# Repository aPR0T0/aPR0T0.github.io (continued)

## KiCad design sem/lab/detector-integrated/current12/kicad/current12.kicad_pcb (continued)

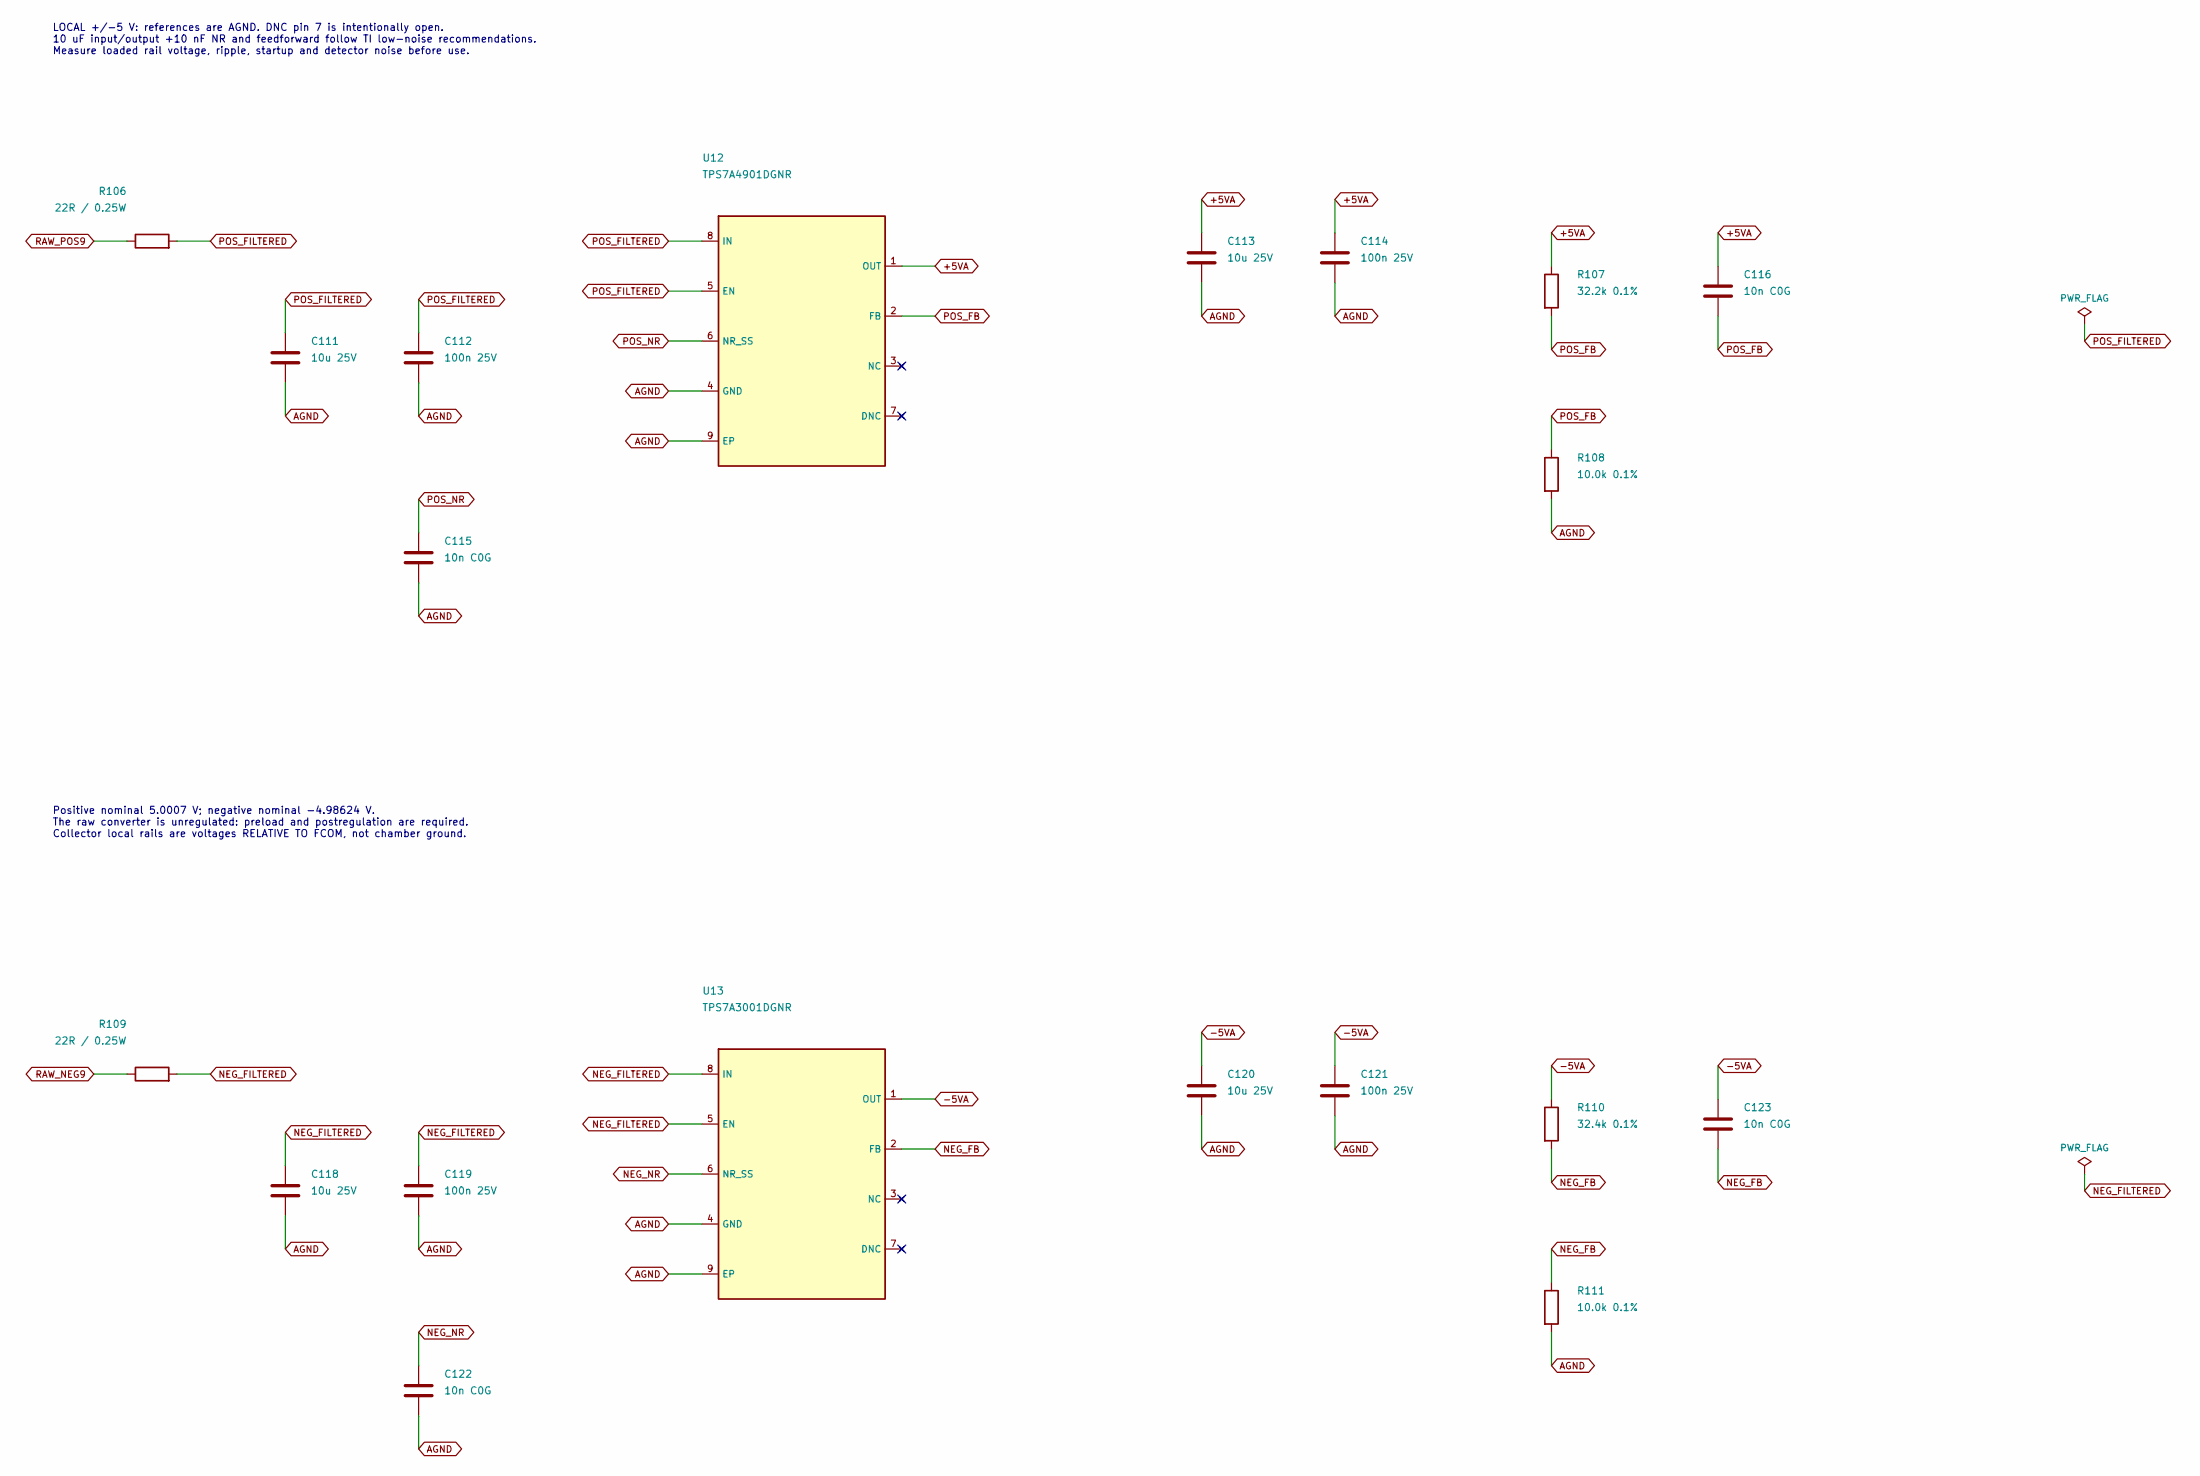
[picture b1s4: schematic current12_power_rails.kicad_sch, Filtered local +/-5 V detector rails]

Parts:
C111, C113, C118, C120: 10u 25V; C_1210_3225Metric
C112, C114, C119, C121: 100n 25V; C_0805_2012Metric
C115, C116, C122, C123: 10n C0G; C_0805_2012Metric
R106, R109: 22R / 0.25W; R_1206_3216Metric
R107: 32.2k 0.1%; R_0805_2012Metric
R108, R111: 10.0k 0.1%; R_0805_2012Metric
R110: 32.4k 0.1%; R_0805_2012Metric
U12: TPS7A4901DGNR; TPS7A_DGN8_TI; MPN TPS7A4901DGNR
U13: TPS7A3001DGNR; TPS7A_DGN8_TI; MPN TPS7A3001DGNR

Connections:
+5VA: C113.1, C114.1, C116.1, R107.1, U12.1 (OUT); also elsewhere on the board
-5VA: C120.1, C121.1, C123.1, R110.1, U13.1 (OUT); also elsewhere on the board
AGND: C111.2, C112.2, C113.2, C114.2, C115.2, C118.2, C119.2, C120.2, C121.2, C122.2, R108.2, R111.2, U12.4 (GND), U12.9 (EP), U13.4 (GND), U13.9 (EP); also elsewhere on the board
NEG_FB: C123.2, R110.2, R111.1, U13.2 (FB)
NEG_FILTERED: C118.1, C119.1, R109.2, U13.5 (EN), U13.8 (IN)
NEG_NR: C122.1, U13.6 (NR_SS)
POS_FB: C116.2, R107.2, R108.1, U12.2 (FB)
POS_FILTERED: C111.1, C112.1, R106.2, U12.5 (EN), U12.8 (IN)
POS_NR: C115.1, U12.6 (NR_SS)
RAW_NEG9: R109.1; also elsewhere on the board
RAW_POS9: R106.1; also elsewhere on the board

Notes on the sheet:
LOCAL +/-5 V: references are AGND. DNC pin 7 is intentionally open. 10 uF input/output +10 nF NR and feedforward follow TI low-noise recommendations. Measure loaded rail voltage, ripple, startup and detector noise before use.
Positive nominal 5.0007 V; negative nominal -4.98624 V. The raw converter is unregulated: preload and postregulation are required. Collector local rails are voltages RELATIVE TO FCOM, not chamber ground.

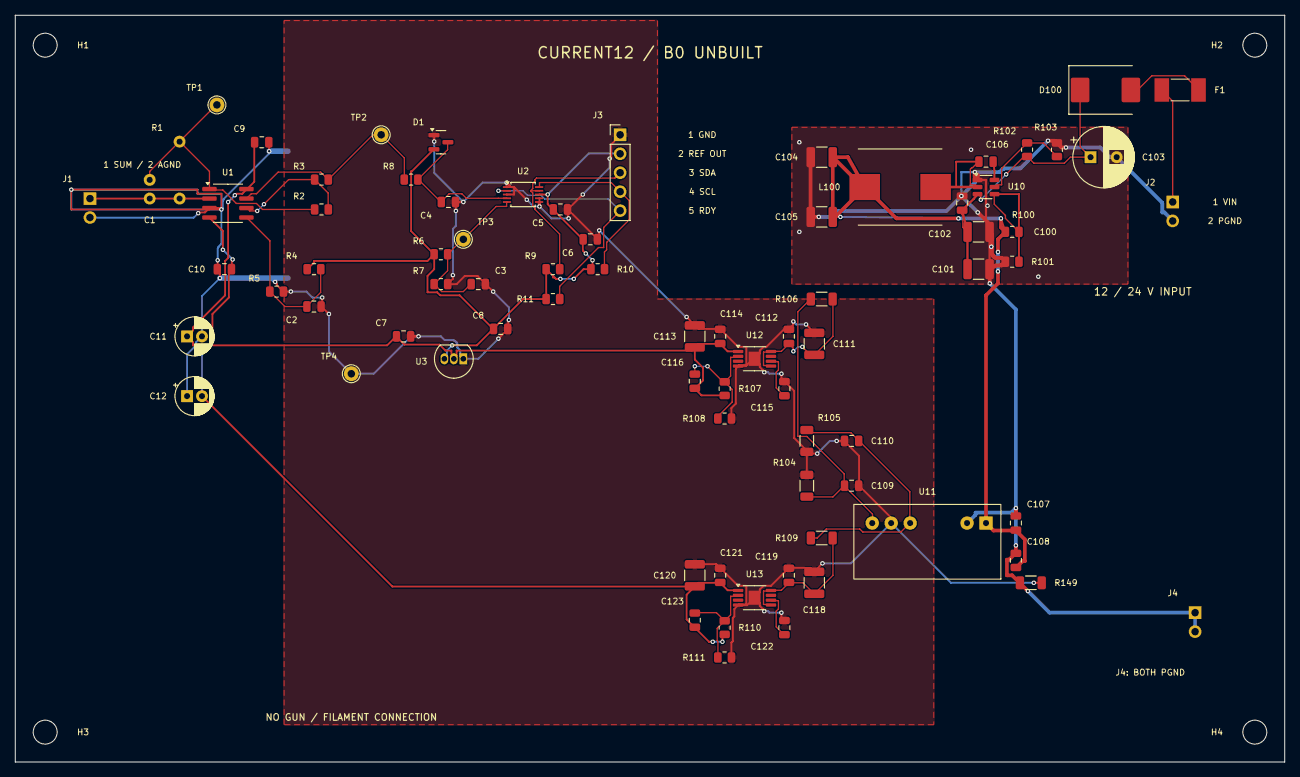
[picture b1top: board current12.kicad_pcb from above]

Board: 2 copper layers, 170.0 x 100.0 mm, 82 parts (0 on the bottom side), 31 nets.

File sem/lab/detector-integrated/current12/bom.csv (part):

Reference,Value,Quantity,MPN_or_procurement_spec,Footprint,Function,Datasheet
U1,LMC662AIM,1,LMC662AIMX/NOPB,Package_SO:SOIC-8_3.9x4.9mm_P1.27mm,"Dual CMOS TIA / attenuator; solder directly, no socket",https://www.ti.com/lit/ds/symlink/lmc662.pdf
R1,100M 1%,1,HVA05FA100M,Resistor_THT:R_Axial_DIN0207_L6.3mm_D2.5mm_P7.62mm_Horizontal,100M axial 6x2.5mm body; tolerance calibrates,
C1,10p C0G,1,10p C0G,Capacitor_THT:C_Disc_D3.0mm_W1.6mm_P2.50mm,"TIA stability, tau=1ms nominal; real input capacitance must be tested",
J1,SPECIMEN / SHIELD,1,SPECIMEN / SHIELD,Connector_PinHeader_2.54mm:PinHeader_1x02_P2.54mm_Vertical,"Direct solder PTFE coax preferred; 1 specimen, 2 shield/chamber",
R2,40.2k 0.1%,1,40.2k 0.1%,Resistor_SMD:R_0805_2012Metric,Attenuator input,
R3,10.0k 0.1%,1,10.0k 0.1%,Resistor_SMD:R_0805_2012Metric,Attenuator feedback,
R4,15.0k 0.1%,1,15.0k 0.1%,Resistor_SMD:R_0805_2012Metric,VBIAS upper divider,
R5,10.0k 0.1%,1,10.0k 0.1%,Resistor_SMD:R_0805_2012Metric,VBIAS lower divider,
C2,1u 10V X7R,1,1u 10V X7R,Capacitor_SMD:C_0805_2012Metric,Quiet 1.32V filter,
R6,1.00k 0.1%,1,1.00k 0.1%,Resistor_SMD:R_0805_2012Metric,ADC midpoint divider upper / rail bleeder,
R7,1.00k 0.1%,1,1.00k 0.1%,Resistor_SMD:R_0805_2012Metric,ADC midpoint divider lower,
C3,10u 10V X7R,1,10u 10V X7R,Capacitor_SMD:C_0805_2012Metric,1.65V reference filter,
R8,820R,1,820R,Resistor_SMD:R_0805_2012Metric,ADC overload current limit; downstream of sensitive node,
C4,100n,1,100n,Capacitor_SMD:C_0805_2012Metric,ADC local RC filter,
D1,BAT54S,1,BAT54S,Package_TO_SOT_SMD:SOT-23,ADC-only Schottky clamp; never on SUM,https://assets.nexperia.com/documents/data-sheet/BAT54S.pdf
U2,ADS1115IDGS,1,ADS1115IDGSR,Package_SO:TSSOP-10_3x3mm_P0.5mm,Differential AIN0-AIN1; I2C0x48; PGA +/-256mV 128SPS defaults,https://www.ti.com/lit/ds/symlink/ads1115.pdf
R9,4.7k,1,4.7k,Resistor_SMD:R_0805_2012Metric,I2C pull-up,
R10,4.7k,1,4.7k,Resistor_SMD:R_0805_2012Metric,I2C pull-up,
R11,10k,1,10k,Resistor_SMD:R_0805_2012Metric,Optional ready open-drain pull-up,
C5,100n,1,100n,Capacitor_SMD:C_0805_2012Metric,ADC local bypass,
C6,1u 10V,1,1u 10V,Capacitor_SMD:C_0805_2012Metric,ADC local bulk bypass,
J3,ESP32 I2C / REF,1,ESP32 I2C / REF,Connector_PinHeader_2.54mm:PinHeader_1x05_P2.54mm_Vertical,1GND 2REF3V3OUT 3GPIO21 4GPIO22 5RDY optional (NC default); ESP powered separately,
U3,MCP1700-3302E/TO,1,MCP1700-3302E/TO,Package_TO_SOT_THT:TO-92_Inline,3.3V ADC supply derived from +5V; max input6V,https://www.microchip.com/content/dam/mchp/documents/APID/Pr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
C7,1u 10V,1,1u 10V,Capacitor_SMD:C_0805_2012Metric,LDO input bypass,
C8,1u 10V,1,1u 10V,Capacitor_SMD:C_0805_2012Metric,LDO required output capacitor,
C9,100n,1,100n,Capacitor_SMD:C_0805_2012Metric,LMC positive rail local bypass,
C10,100n,1,100n,Capacitor_SMD:C_0805_2012Metric,LMC negative rail local bypass,
C11,10u 16V,1,10u 16V,Capacitor_THT:CP_Radial_D5.0mm_P2.00mm,Positive rail bulk; positive lead to+5V,
C12,10u 16V,1,10u 16V,Capacitor_THT:CP_Radial_D5.0mm_P2.00mm,Negative rail bulk; positive lead toAGND,
TP1,TIA,1,TIA,TestPoint:TestPoint_THTPad_D2.0mm_Drill1.0mm,Low impedance measurement only,
TP2,ADC_DRIVE,1,ADC_DRIVE,TestPoint:TestPoint_THTPad_D2.0mm_Drill1.0mm,Low impedance measurement only,
TP3,VMID,1,VMID,TestPoint:TestPoint_THTPad_D2.0mm_Drill1.0mm,Low impedance measurement only,
TP4,AGND,1,AGND,TestPoint:TestPoint_THTPad_D2.0mm_Drill1.0mm,Low impedance measurement only,
H1,M3,1,M3,MountingHole:MountingHole_3.2mm_M3,Unplated mounting hole; insulating standoff,
H2,M3,1,M3,MountingHole:MountingHole_3.2mm_M3,Unplated mounting hole; insulating standoff,
H3,M3,1,M3,MountingHole:MountingHole_3.2mm_M3,Unplated mounting hole; insulating standoff,
H4,M3,1,M3,MountingHole:MountingHole_3.2mm_M3,Unplated mounting hole; insulating standoff,
J4,CHAMBER / OUTER SHIELD,1,CHAMBER / OUTER SHIELD,Connector_PinHeader_2.54mm:PinHeader_1x02_P2.54mm_Vertical,"Chamber, enclosure, outer shield; never FCOM",
J2,12/24V DC INPUT,1,12/24V DC INPUT,Connector_PinHeader_2.54mm:PinHeader_1x02_P2.54mm_Vertical,1: positive regulated 9-30 V DC; 2: return. Current-limited source; no mains input.,
F1,1A FAST / 125V,1,0451001.MRL,Fuse:Fuse_Littelfuse-NANO2-451_453,Input wiring/fault fuse; verify converter and input-capacitor inrush against time-current and I-squared-t limits.,https://www.littelfuse.com/products/fuses-overcurrent-protec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
D100,SS36 / 60V,1,SS36-E3/57T,Diode_SMD:D_SMC,"Series reverse-input protection. Pin 1 cathode to protected input; pin 2 anode to fuse. This exact Vishay part is SMC, not SMA.",https://www.vishay.com/docs/88751/ss32.pdf
C100,4.7u 50V,1,4.7u 50V,Capacitor_SMD:C_1210_3225Metric,First buck input capacitor: direct short loop to U10 VIN/GND.,
C101,4.7u 50V,1,4.7u 50V,Capacitor_SMD:C_1210_3225Metric,Second buck input capacitor; total nominal input 9.4 uF.,
C102,100n 50V,1,100n 50V,Capacitor_SMD:C_0805_2012Metric,HF input bypass; shortest possible VIN-to-GND loop.,
C103,22u 50V,1,22u 50V,Capacitor_THT:CP_Radial_D8.0mm_P3.50mm,"22 uF 50 V aluminum, body <=8 mm, leads formed to 3.5 mm pitch; connector-side input bulk. Positive at protected input.",
U10,LMR51420XF,1,LMR51420XFDDCR,Package_TO_SOT_SMD:SOT-23-6,"500 kHz forced-PWM synchronous buck, 4.5-36 V operating. 9-30 V regulated input is the board limit; no automotive surge qualification.",https://www.ti.com/lit/ds/symlink/lmr51420.pdf
L100,10uH / 12A Isat,1,SRP1038A-100M,Integrated:Bourns_SRP1038A,"10 uH, 7.5 A RMS, 12 A Isat, 30 mOhm max. Isat exceeds 5.1 A maximum buck current-limit threshold. Nonpolar.",https://www.bourns.com/docs/product-datasheets/srp1038a.pdf
C104,22u 25V,1,22u 25V,Capacitor_SMD:C_1210_3225Metric,X7R; verify effective capacitance at operating voltage,
C105,22u 25V,1,22u 25V,Capacitor_SMD:C_1210_3225Metric,X7R; verify effective capacitance at operating voltage,
C106,100n 25V,1,100n 25V,Capacitor_SMD:C_0805_2012Metric,Bootstrap capacitor directly between U10 pin 6 CB and pin 2 SW.,
R100,101k 0.1%,1,101k 0.1%,Resistor_SMD:R_0805_2012Metric,Buck feedback top: 0.6*(1+101/13.5) = 5.08889 V nominal. Both divider resistors must be 0.1% to preserve the reviewed module/supervisor voltage margin.,
R101,13.5k 0.1%,1,13.5k 0.1%,Resistor_SMD:R_0805_2012Metric,Buck feedback bottom; Kelvin reference to PGND at input-capacitor return.,
R102,1.00M 1%,1,1.00M 1%,Resistor_SMD:R_0805_2012Metric,"EN divider top: nominal 7.38 V rising UVLO, below accepted 9 V input after series diode.",
R103,200k 1%,1,200k 1%,Resistor_SMD:R_0805_2012Metric,EN divider bottom; about 6.6 V falling UVLO. EN cannot float.,
U11,R05P09D/P,1,R05P09D/P,Integrated:R05P09D_SIP7,"5 V to unregulated +/-9 V, 55 mA each; 1 W. Basic 250 VAC rms working isolation, 4-10 pF; 6.4 kV DC is a 1-second test only. /P gives continuous short protection.",https://www.recom-power.com/pdf/Econoline/RxxPxx.pdf
C107,1u 25V,1,1u 25V,Capacitor_SMD:C_0805_2012Metric,Local primary bypass at the isolation module input pins.,
C108,100n 25V,1,100n 25V,Capacitor_SMD:C_0805_2012Metric,HF primary bypass; does not cross the isolation barrier.,
C109,1u 25V,1,1u 25V,Capacitor_SMD:C_0805_2012Metric,X7R; verify effective capacitance at operating voltage,
C110,1u 25V,1,1u 25V,Capacitor_SMD:C_0805_2012Metric,X7R; verify effective capacitance at operating voltage,
R104,1.30k / 0.25W,1,1.30k / 0.25W,Resistor_SMD:R_1206_3216Metric,Raw positive preload >=6.23 mA at 8.1 V (>10% of 55 mA rail rating).,
R105,1.30k / 0.25W,1,1.30k / 0.25W,Resistor_SMD:R_1206_3216Metric,Raw negative preload. Validate cross-regulation with actual asymmetric load.,
R149,0R STAR BOND,1,0R STAR BOND,Resistor_SMD:R_1206_3216Metric,Intentional single-point ground bond for near-ground specimen detector. Fitted 0 ohm; omitted entirely on collector variant.,
R106,22R / 0.25W,1,22R / 0.25W,Resistor_SMD:R_1206_3216Metric,Series differential ripple filter; 22 ohm with 10 uF gives a 723 Hz nominal pole. Raw preload is before this resistor.,
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
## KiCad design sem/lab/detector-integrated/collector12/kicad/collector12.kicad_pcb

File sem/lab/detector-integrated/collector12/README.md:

# Biased-collector board · collector12

Collector12 · B0 · unbuilt. A separate metal collector measures net arriving electron current. The bias converter raises FCOM, which is the common for the amplifier, ADC and local MCU. Two onboard optocouplers connect that floating section to the grounded scan ESP32.

Input: 12 / 24 V · regulated 9–30 V. Local rails: ±5 V around FCOM · local 3.3 V.

## Exact external connections

Connector pin numbers, not screen orientation, define the wiring. Pin 1 uses the marked / square pad in the native footprint. Match this revision before assembly.

| Pin | Net | External connection | Detail |
|---|---|---|---|
| J2.1 | VIN | DC source +12 V or +24 V | Use regulated 9–30 V; this powers detector electronics and bias only. |
| J2.2 | PGND | DC source negative | Ground-side return. |
| J1.1 | SUM | Separate metal collector | Insulated feedthrough centre. Never connect the bias output directly to this pin. |
| J1.2 | FCOM | Inaccessible inner guard | Floats near +200 V. Keep the outer cable shield and enclosure separately grounded. |
| J3.1 | PGND | ESP32 GND | All J3 pins are on the grounded side. |
| J3.2 | HOST_VIO | ESP32 3.3 V rail | Required interface supply INPUT, ≤19 mA planning allowance. Using the host’s rail removes the board-powered LED/pull-up injection path; leakage and hot-plug behavior remain unverified. |
| J3.3 | HOST_TX | ESP32 GPIO17 · UART TX | Host → optocoupler → floating MCU RX. |
| J3.4 | HOST_RX | ESP32 GPIO16 · UART RX | Floating MCU TX → optocoupler → host. |
| J3.5 | HV_ENABLE | ESP32 GPIO32 | LOW by default. HIGH enables the current-limited bias supply; actual rail qualification still holds the command clamp. |
| J3.6 | PGM_RELEASE | ESP32 GPIO33 | LOW clamps programming to zero. HIGH only after startup; hardware also requires the actual module rail to pass its delayed check. |
| J3.7 | HV_FAULT_N | ESP32 GPIO34 · input | Active-LOW current-limiter fault; board pulls up to HOST_VIO. A fault blanks acquisition and disables bias. |
| J3.8 | PGND | ESP32 GND / optional duplicate return | Same ground-side net as J3.1. |
| J4.1 | PGND | Chamber / enclosure ground star | Ground the specimen in this collector-only arrangement. Accessible metal also needs its own secure earth bond. |
| J4.2 | PGND | Same ground star / shield return | Duplicate PGND terminal; keep this separate from the floating inner guard. |
| J5.1 | MISO | AVR programmer MISO · only with bias discharged | Standard 2×3 ICSP; remove every programmer lead before bias operation. |
| J5.2 | +3V3D | Programmer target-voltage sense | 3.3 V logic only; do not back-power the island. |
| J5.3 | SCK | AVR programmer SCK | Configure an external 8 MHz crystal and suitable ICSP clock. |
| J5.4 | MOSI | AVR programmer MOSI | Commission with HV disabled and verified discharged. |
| J5.5 | RESET | AVR programmer RESET | Not a ground-side control signal. |
| J5.6 | FCOM | AVR programmer ground · commissioning only | Disconnect programmer entirely before collector bias is enabled. |

## Design files

- Open `kicad/collector12.kicad_pro` with KiCad 10. The complete design ZIP includes all hierarchical sheets and local libraries.
- `exports/schematic.pdf` contains every schematic sheet.
- `exports/assembly.svg` identifies the component positions.
- `bom.csv` contains the selected parts; prices are not quoted.
- `verification/check-summary.json` records native checks and checked-file hashes.
- `fabrication.zip` contains prototype manufacturing outputs. Inspection and bench commissioning remain required.

Collector firmware and setup notes are in the firmware folder of the complete package. J3.2 is a HOST_VIO **input** from the ESP32’s own 3.3 V rail. The two UART paths use onboard optocouplers.

---

## Shared architecture and commissioning

Two unbuilt PCB prototypes extend the original LMC662 / ADS1115 detector. Use the [interactive board and pin guide](https://apr0t0.github.io/sem/lab/power.html) to select specimen current or the positive collector. Both accept a regulated 9–30 V input, including nominal 12 V and 24 V. This supply powers detector electronics and collector bias; the electron gun, scan drivers and grounded ESP32 have separate supplies.

## What is onboard

Input fuse and reverse-polarity diode → LMR51420 500 kHz buck → approximately 5.09 V → RECOM R05P09D/P isolated raw ±9 V → RC filtering → TPS7A49 / TPS7A30 local ±5 V. The ADC runs from its own 3.3 V supply regulator. The collector also has a separate digital 3.3 V rail, an ATmega328P and two VO2611-X016 optocouplers.

The collector's XP Power CA02P-5 module is soldered onto the same board. It creates programmable 0–200 V from the onboard 5 V bus. Two 10 kΩ filter stages and 100 nF / 1 µF capacitors feed FCOM. Nominal FCOM at a raw 200 V is about 199.6 V because of bleeder loading. A TPS2553-1 latch-off switch limits the bias-module input: 88.7 kΩ / 1% programs a calculated 262–342 mA range, below the module’s 420 mA short-protection input limit. Its active-LOW fault goes through J3.7 to ESP32 GPIO34. Verify startup and current-limit behavior on the assembled board. Program linearity is specified from 15% of full scale, so treat low-bias settings as requiring calibration.

The isolated supply and HV converter are packaged modules; the buck is a discrete IC / inductor circuit. This is a self-contained onboard power design, not an entirely discrete magnetics design. Obtain current distributor quotes: the HV module may dominate cost.

Both layouts use local top/bottom PGND copper and six stitching vias around the buck's ground returns. The amplifier's C9/C10 bypass capacitors have direct 0.75 mm returns to the quiet AGND or FCOM plane. The guarded SUM trace and its no-plane region remain separate. These filled-copper connections were inspected in the native boards; their noise performance still requires measurement.

## Choose the current path

| Connection | Specimen-current board | Collector board |
|---|---|---|
| J1.1 SUM | Insulated conductive specimen holder | Separate insulated metal collector |
| J1.2 guard | AGND, near chamber ground | FCOM, near positive collector bias |
| Specimen | Only through SUM; insulated from stage | Grounded conductive contact |
| Local analog common | Deliberately bonded to PGND/chamber | Elevated FCOM |
| J3 data | Direct 3.3 V I²C to ESP32 | Ground-side UART through two optocouplers |
| Extra bias | None | Generated and filtered onboard |

The specimen-current board’s direct I²C is not isolated during power-off. Keep both host and detector powered while connected, using coordinated power; disconnect the interface before separately power-cycling either side. The collector uses host-powered VIO at J3.2 for its ground-side UART interface.

SUM is the amplifier input. The positive bias connects to FCOM, never directly to SUM; a direct bias wire would bypass the measurement. At steady state, unsaturated feedback holds SUM close to the amplifier's local common. The collector reading is net collected electron current, potentially a mixture of SE, BSE and background. There is no charge multiplication on a plain metal collector. An insulating specimen still needs a charging solution.

## Collector boundary

The complete analog circuit, ADS1115 and ATmega328P operate relative to FCOM. The primary side, CA converter case/return, outer enclosure, accessible cable shield, grounded specimen and scan ESP32 operate relative to chamber ground. Only the rated isolated converter, two optocouplers and deliberate filtered bias network bridge these references. No grounded USB, programming or oscilloscope cable belongs on FCOM while biased.

Mount the collector PCB on nylon / PEEK standoffs with insulating fasteners. Four 3.2 mm holes reserve a maximum 6.4 mm diameter insulating washer envelope. A grounded screw head is not an electrically neutral hole: maintain separation from grounded metal above and below the floating copper.

The PCB design enforces a 5 mm copper separation between primary and FCOM regions and a separate 2 mm rule between grounded-side HV and low-voltage conductors. These are layout rules, not certification. RECOM's 250 VAC rms basic working insulation is the relevant published working specification; 6.4 kV is a brief test rating. Converter and optocoupler capacitance still carries displacement current. Rail filters cannot remove every path for common-mode pickup.

## Collector startup and shutdown

1. Verify component orientations, cleanliness, connector numbering and the exact BOM. Assemble and inspect the input power stages before fitting the high-impedance parts where practical.
2. With the electron beam blanked and the HV module disabled, power from a current-limited regulated source. Verify 5 V bus, ±9 V raw rails, ±5 V local rails and both 3.3 V domains using their correct reference. Repeat at 12 V and 24 V and across expected loads.
3. Program the ATmega328P for an external 8 MHz crystal and 3.3 V operation with bias disabled and verified discharged. Remove all ICSP connections. Connect the grounded ESP32 via the specified UART, two control pins and active-LOW fault input. Feed collector J3.2 HOST_VIO from the ESP32’s 3.3 V rail (allow 19 mA); this removes the board-powered LED/pull-up injection path into host GPIO. Leakage and hot-plug behavior remain unverified. On the specimen-current board, J3.2 is instead a reference output and is left open.
4. Begin with the bias pot at minimum. The ESP32 first confirms the optical link. Its `b` command raises HV_ENABLE while holding PGM_RELEASE LOW for at least 100 ms, then releases the buffered RC ramp. Hardware also uses a TPS3808G50 to qualify the actual module 5 V rail, with a datasheet delay of 180–420 ms before allowing PGM_RELEASE to release the clamp. The buffer remains powered from the unswitched 5 V bus. A 10 kΩ / 47 µF command filter gives about 0.47–0.59 s nominal ramp time; effective capacitance and leakage must be checked. The sketch keeps the beam blanked for a 10 s initial settling policy and checks the optical link during that interval. That delay is a starting policy, not a guarantee of pA settling. Measure the actual bias rise, overshoot and settling before deciding the interval is adequate.
5. With bias steady and beam blanked, use `z` to measure a new zero. Only then use `s` for a scan. Repeat zero after any bias adjustment. The acquisition sequence requests fresh ADC conversions; CRC, request IDs, status and timeouts reject incomplete or stale replies.
6. `x` aborts, blanks the beam, clamps programming to zero and removes the CA module's 5 V input. Passive bleeders remain connected. Check voltage with a rated instrument before touching or attaching a programmer; a software OFF state is not proof of discharge.

The final 1 µF capacitor alone stores 20 mJ at 200 V. Its independent 9.98 MΩ bleeder has a 9.98 s time constant, but additional paths and unspecified module internal capacitance affect whole-assembly discharge. Measure the complete assembly, including cables and relevant faults. These software controls are not a certified beam interlock.

## Proving that readings are electrons

- Inject a known local current into SUM at zero bias and elevated bias. Establish gain, sign, offset, clipping and settling with the real cable and feedthrough.
- Log the collector dark current with pumps, heater, converters and UART operating. Repeat a raster with the beam blanked and then blocked upstream; image structure under those conditions is pickup.
- Compare repeated scans and measured incident beam current. Repeat at fixed, settled bias values. Separate bias-dependent leakage and displacement current from collection changes.
- Record raw ADC codes, zero, calibration, timing, measured bias and all faults. A clean DRC does not establish a picoampere noise floor.

The board-specific package contains the exact connector schedule, native CAD, BOM, CAD results and prototype fabrication outputs. The original externally powered Rev A and the earlier battery / fibre collector concept remain separate options on their original pages.

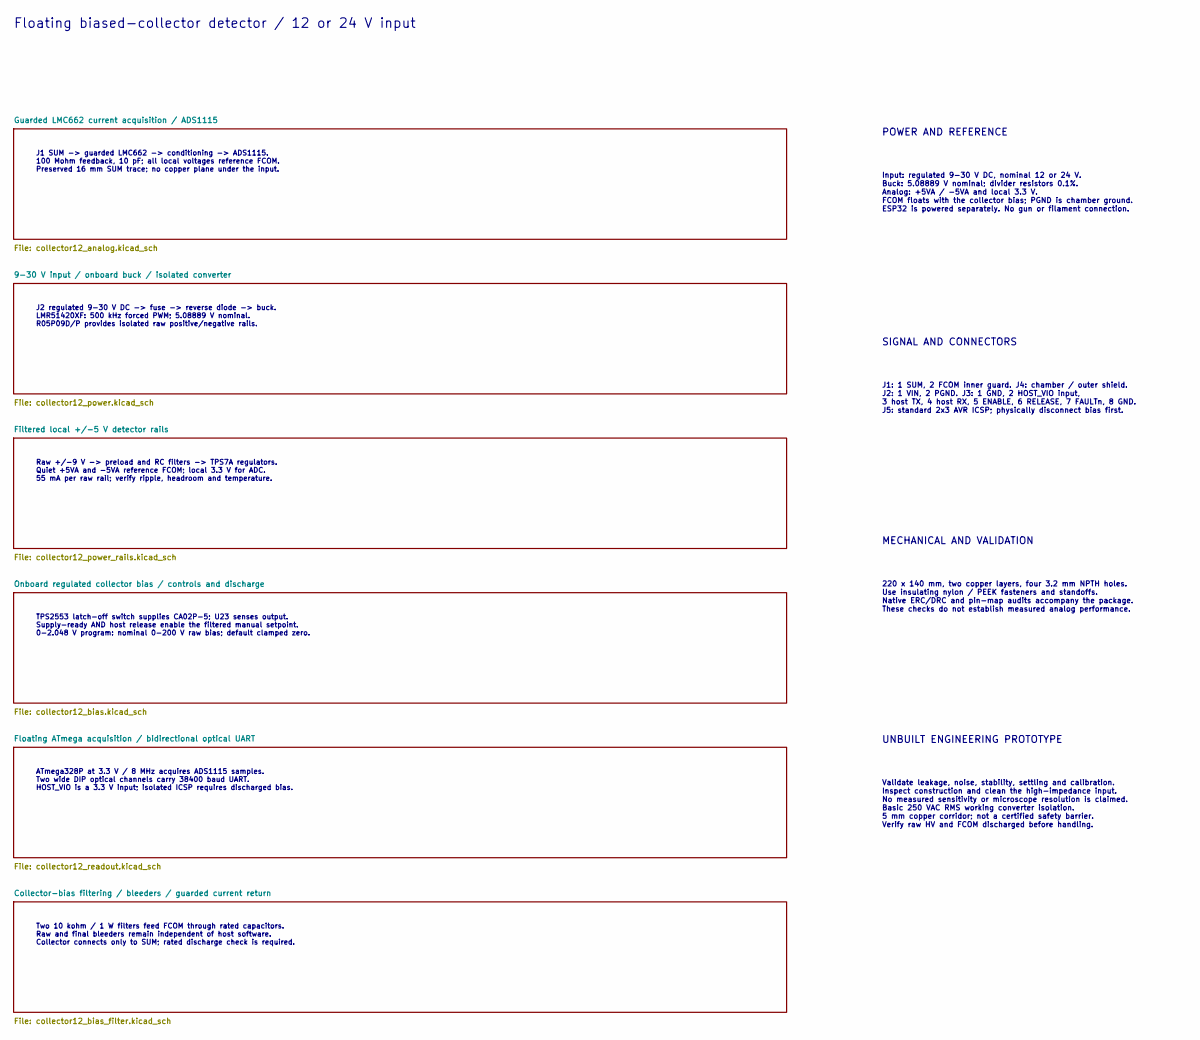
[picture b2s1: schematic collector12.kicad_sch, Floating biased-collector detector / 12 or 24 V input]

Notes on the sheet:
Floating biased-collector detector / 12 or 24 V input
J1 SUM -> guarded LMC662 -> conditioning -> ADS1115. 100 Mohm feedback, 10 pF; all local voltages reference FCOM. Preserved 16 mm SUM trace; no copper plane under the input.
J2 regulated 9-30 V DC -> fuse -> reverse diode -> buck. LMR51420XF: 500 kHz forced PWM; 5.08889 V nominal. R05P09D/P provides isolated raw positive/negative rails.
Raw +/-9 V -> preload and RC filters -> TPS7A regulators. Quiet +5VA and -5VA reference FCOM; local 3.3 V for ADC. 55 mA per raw rail; verify ripple, headroom and temperature.
TPS2553 latch-off switch supplies CA02P-5; U23 senses output. Supply-ready AND host release enable the filtered manual setpoint. 0-2.048 V program: nominal 0-200 V raw bias; default clamped zero.
ATmega328P at 3.3 V / 8 MHz acquires ADS1115 samples. Two wide DIP optical channels carry 38400 baud UART. HOST_VIO is a 3.3 V input; isolated ICSP requires discharged bias.
Two 10 kohm / 1 W filters feed FCOM through rated capacitors. Raw and final bleeders remain independent of host software. Collector connects only to SUM; rated discharge check is required.
POWER AND REFERENCE
Input: regulated 9-30 V DC, nominal 12 or 24 V. Buck: 5.08889 V nominal; divider resistors 0.1%. Analog: +5VA / -5VA and local 3.3 V. FCOM floats with the collector bias; PGND is chamber ground. ESP32 is powered separately. No gun or filament connection.
SIGNAL AND CONNECTORS
J1: 1 SUM, 2 FCOM inner guard. J4: chamber / outer shield. J2: 1 VIN, 2 PGND. J3: 1 GND, 2 HOST_VIO input, 3 host TX, 4 host RX, 5 ENABLE, 6 RELEASE, 7 FAULTn, 8 GND. J5: standard 2x3 AVR ICSP; physically disconnect bias first.
MECHANICAL AND VALIDATION
220 x 140 mm, two copper layers, four 3.2 mm NPTH holes. Use insulating nylon / PEEK fasteners and standoffs. Native ERC/DRC and pin-map audits accompany the package. These checks do not establish measured analog performance.
UNBUILT ENGINEERING PROTOTYPE
Validate leakage, noise, stability, settling and calibration. Inspect construction and clean the high-impedance input. No measured sensitivity or microscope resolution is claimed. Basic 250 VAC RMS working converter isolation. 5 mm copper corridor; not a certified safety barrier. Verify raw HV and 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

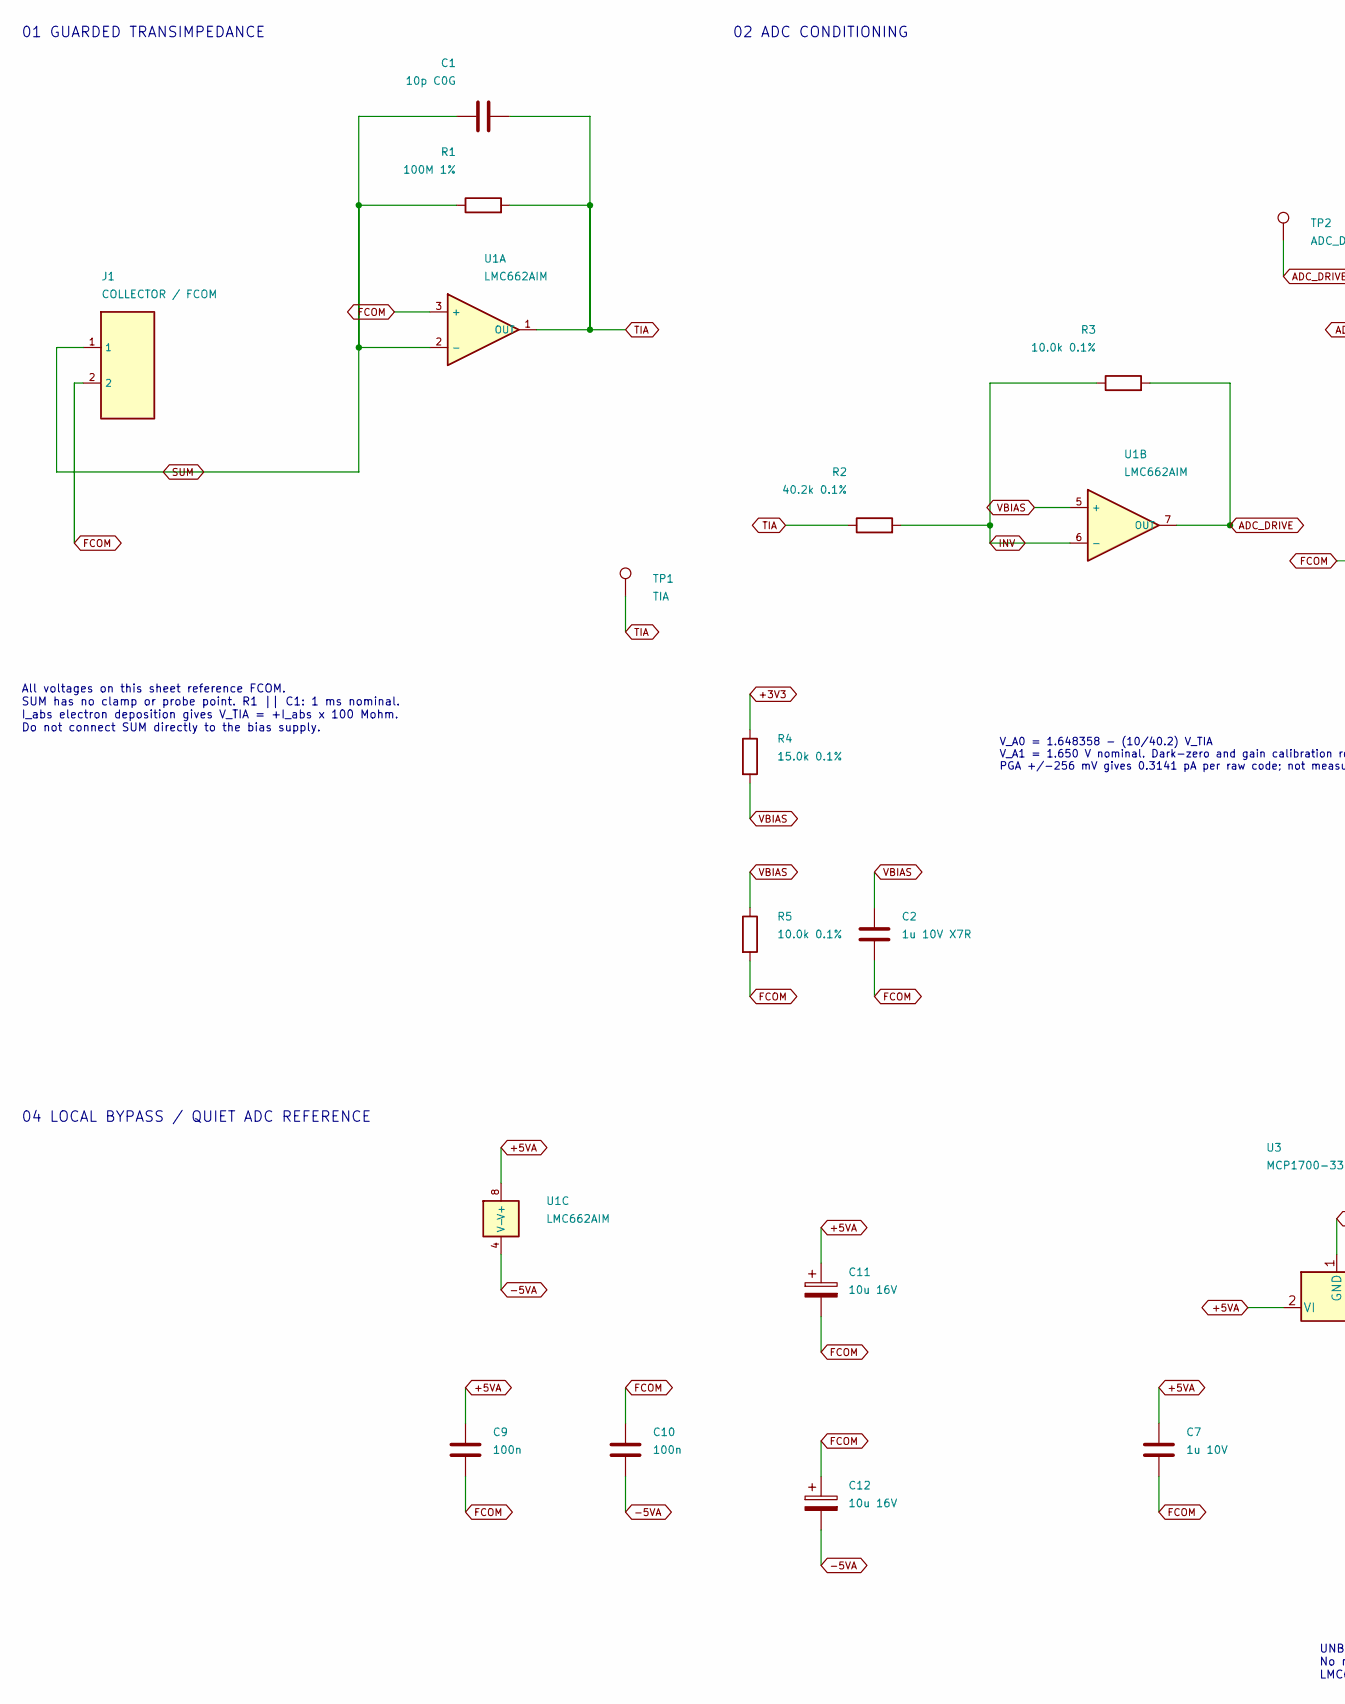
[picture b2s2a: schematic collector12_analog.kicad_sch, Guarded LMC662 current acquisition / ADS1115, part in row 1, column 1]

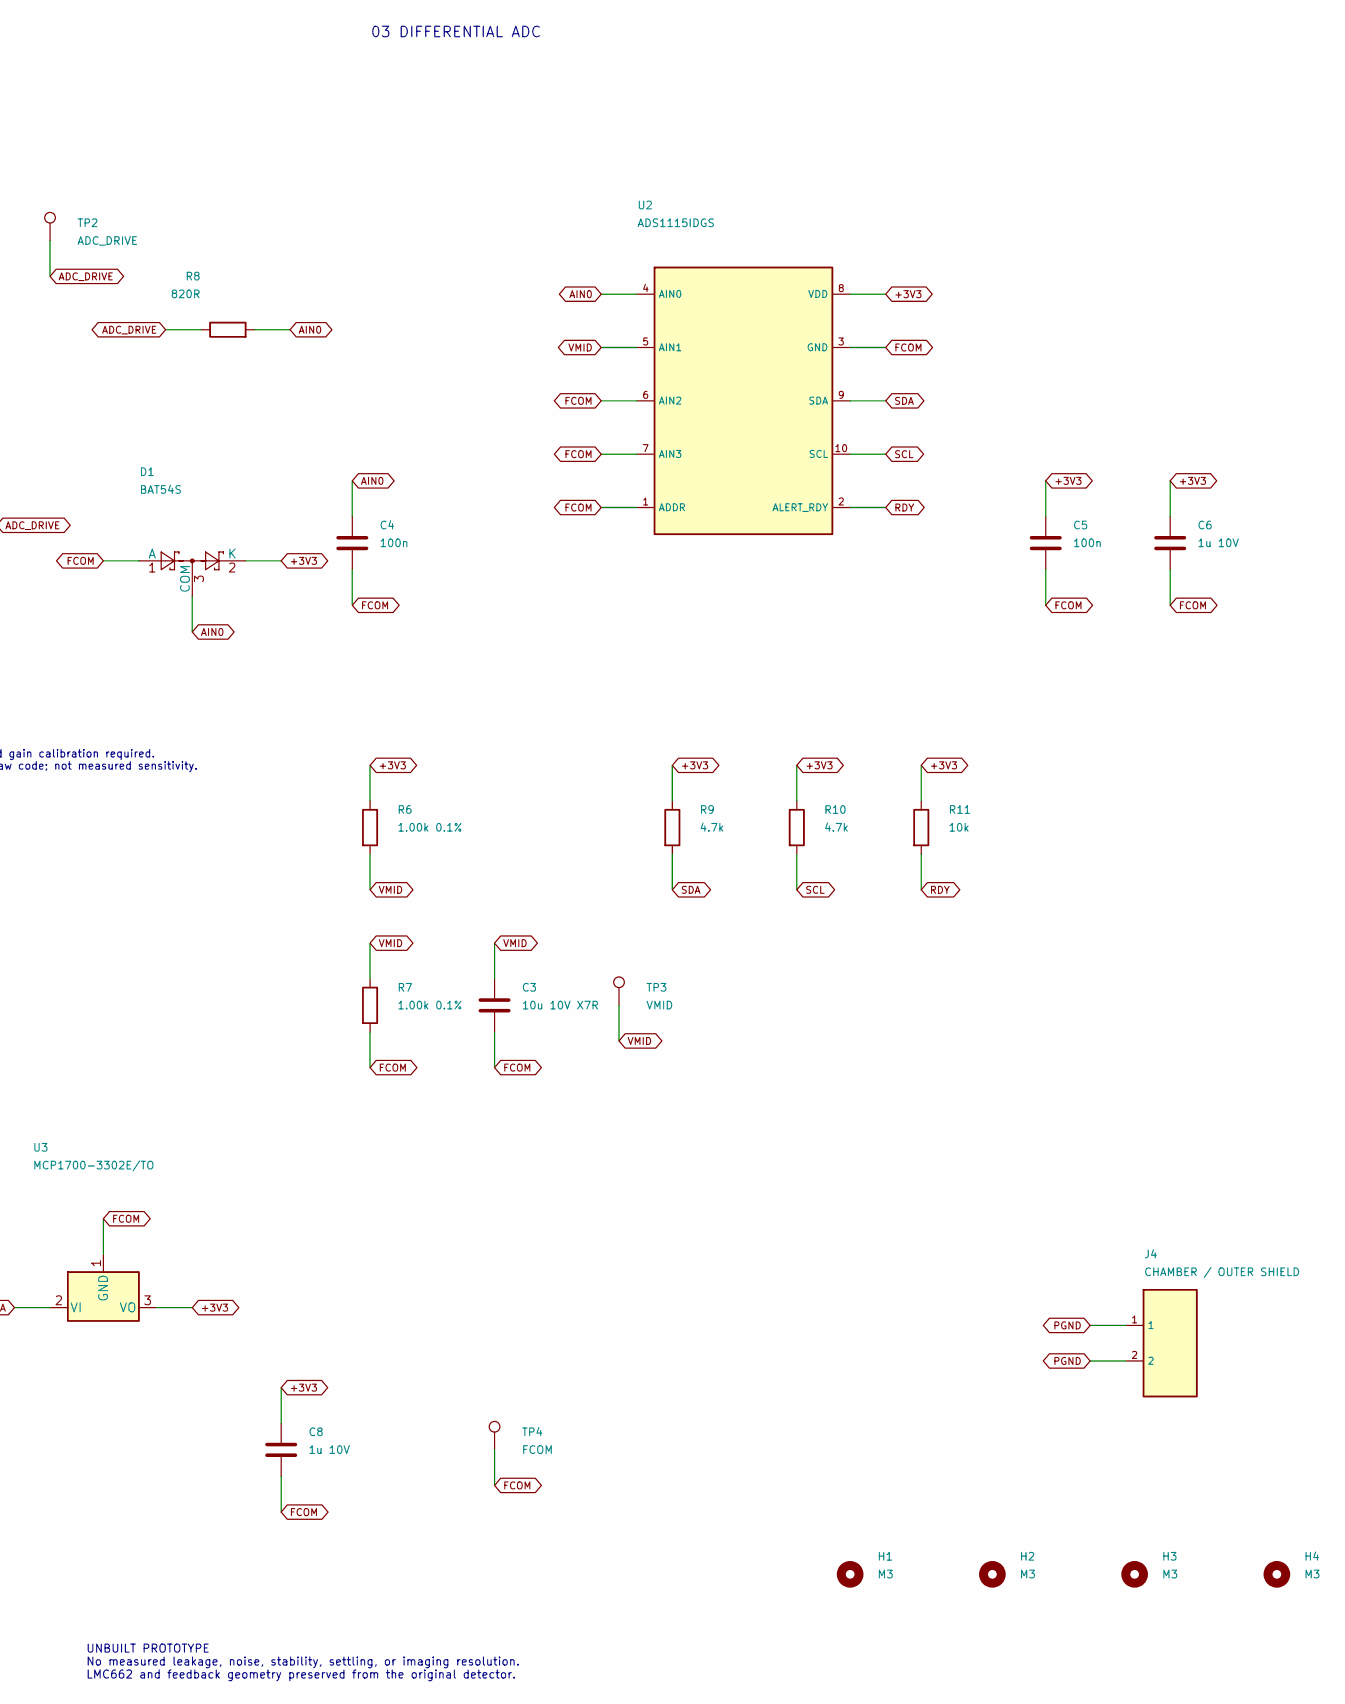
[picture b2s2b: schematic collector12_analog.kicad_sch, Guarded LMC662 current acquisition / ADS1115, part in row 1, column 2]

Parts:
C1: 10p C0G; C_Disc_D3.0mm_W1.6mm_P2.50mm
C2: 1u 10V X7R; C_0805_2012Metric
C3: 10u 10V X7R; C_0805_2012Metric
C4, C5, C9, C10: 100n; C_0805_2012Metric
C6, C7, C8: 1u 10V; C_0805_2012Metric
C11, C12: 10u 16V; CP_Radial_D5.0mm_P2.00mm
D1: BAT54S; SOT-23; MPN BAT54S
H1, H2, H3, H4: M3; MountingHole_3.2mm_M3
J1: COLLECTOR / FCOM; PinHeader_1x02_P2.54mm_Vertical
J4: CHAMBER / OUTER SHIELD; PinHeader_1x02_P2.54mm_Vertical
R1: 100M 1%; R_Axial_DIN0207_L6.3mm_D2.5mm_P7.62mm_Horizontal; MPN HVA05FA100M
R2: 40.2k 0.1%; R_0805_2012Metric
R3, R5: 10.0k 0.1%; R_0805_2012Metric
R4: 15.0k 0.1%; R_0805_2012Metric
R6, R7: 1.00k 0.1%; R_0805_2012Metric
R8: 820R; R_0805_2012Metric
R9, R10: 4.7k; R_0805_2012Metric
R11: 10k; R_0805_2012Metric
TP1: TIA; TestPoint_THTPad_D2.0mm_Drill1.0mm
TP2: ADC_DRIVE; TestPoint_THTPad_D2.0mm_Drill1.0mm
TP3: VMID; TestPoint_THTPad_D2.0mm_Drill1.0mm
TP4: FCOM; TestPoint_THTPad_D2.0mm_Drill1.0mm
U1: LMC662AIM; SOIC-8_3.9x4.9mm_P1.27mm; MPN LMC662AIMX/NOPB
U2: ADS1115IDGS; TSSOP-10_3x3mm_P0.5mm; MPN ADS1115IDGSR
U3: MCP1700-3302E/TO; TO-92_Inline; MPN MCP1700-3302E/TO

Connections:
+3V3: C5.1, C6.1, C8.1, D1.2 (K), R4.1, R6.1, R9.1, R10.1, R11.1, U2.8 (VDD), U3.3 (VO)
+5VA: C7.1, C9.1, C11.1, U1.8 (V+), U3.2 (VI); also elsewhere on the board
-5VA: C10.2, C12.2, U1.4 (V-); also elsewhere on the board
ADC_DRIVE: R3.2, R8.1, TP2.1, U1.7 (OUT)
AIN0: C4.1, D1.3 (COM), R8.2, U2.4 (AIN0)
FCOM: C2.2, C3.2, C4.2, C5.2, C6.2, C7.2, C8.2, C9.2, C10.1, C11.2, C12.1, D1.1 (A), J1.2, R5.2, R7.2, TP4.1, U1.3 (+), U2.1 (ADDR), U2.3 (GND), U2.6 (AIN2), U2.7 (AIN3), U3.1 (GND); also elsewhere on the board
INV: R2.2, R3.1, U1.6 (-)
PGND: J4.1, J4.2; also elsewhere on the board
RDY: R11.2, U2.2 (ALERT_RDY)
SCL: R10.2, U2.10 (SCL); also elsewhere on the board
SDA: R9.2, U2.9 (SDA); also elsewhere on the board
SUM: C1.1, J1.1, R1.1, U1.2 (-)
TIA: C1.2, R1.2, R2.1, TP1.1, U1.1 (OUT)
VBIAS: C2.1, R4.2, R5.1, U1.5 (+)
VMID: C3.1, R6.2, R7.1, TP3.1, U2.5 (AIN1)

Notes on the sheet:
01 GUARDED TRANSIMPEDANCE
02 ADC CONDITIONING
03 DIFFERENTIAL ADC
All voltages on this sheet reference FCOM. SUM has no clamp or probe point. R1 || C1: 1 ms nominal. I_abs electron deposition gives V_TIA = +I_abs x 100 Mohm. Do not connect SUM directly to the bias supply.
V_A0 = 1.648358 - (10/40.2) V_TIA V_A1 = 1.650 V nominal. Dark-zero and gain calibration required. PGA +/-256 mV gives 0.3141 pA per raw code; not measured sensitivity.
04 LOCAL BYPASS / QUIET ADC REFERENCE
UNBUILT PROTOTYPE No measured leakage, noise, stability, settling, or imaging resolution. LMC662 and feedback geometry preserved from the original detector.
